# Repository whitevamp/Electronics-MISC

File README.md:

# Electronics-MISC
I do not own any of the files in this Git repository. I have placed them here for preservation and in the hope that they might be useful to someone. If any of these files belong to you and you would like them removed, please let me know. All these files were publicly available at the time of collection. Additionally, if you find any issues or have concerns about the content, please feel free to reach out to me for further assistance.

## License

This repository is licensed under the Creative Commons Attribution-NonCommercial-ShareAlike 4.0 International (CC BY-NC-SA 4.0). For more information, see the [LICENSE](LICENSE) file.

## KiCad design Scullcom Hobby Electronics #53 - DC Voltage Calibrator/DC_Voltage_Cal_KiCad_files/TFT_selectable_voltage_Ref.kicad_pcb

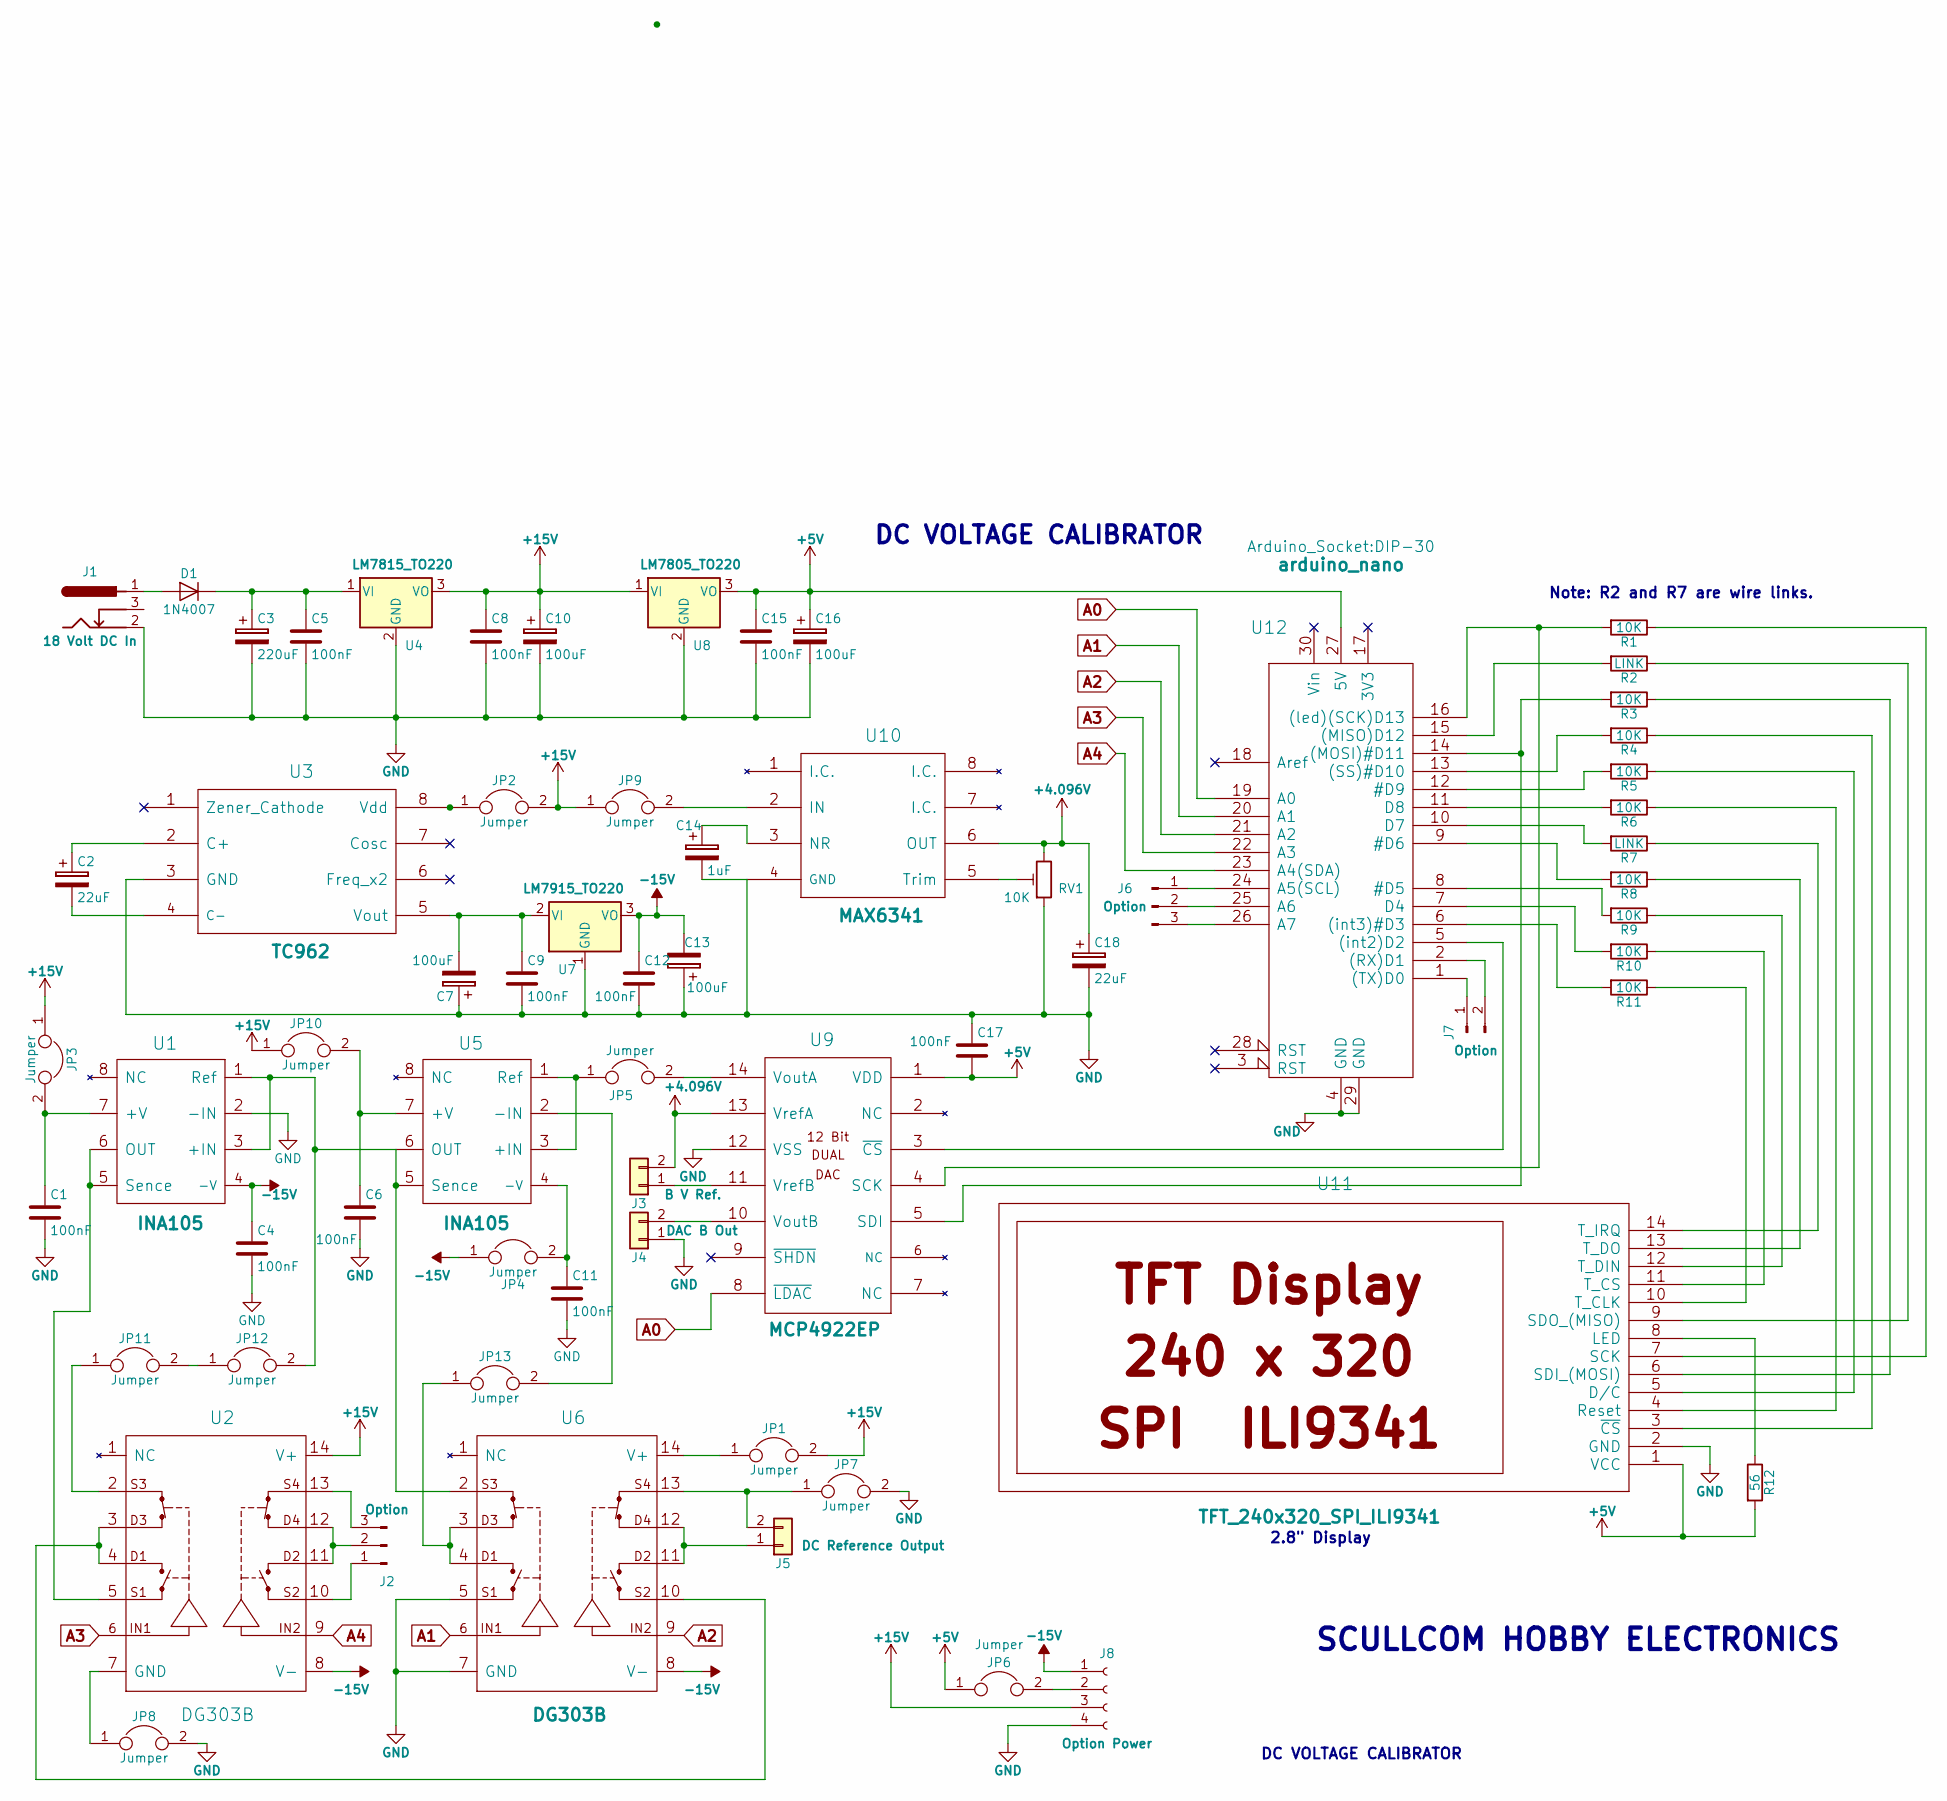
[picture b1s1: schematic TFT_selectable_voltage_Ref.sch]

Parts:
C1, C12: 100nF; C_Rect_L7.2mm_W2.5mm_P5.00mm_FKS2_FKP2_MKS2_MKP2
C2, C18: 22uF; CP_Radial_D5.0mm_P2.00mm
C3: 220uF; CP_Radial_D8.0mm_P5.00mm
C4, C5, C6, C8, C9, C11, C15, C17: 100nF; C_Rect_L7.0mm_W2.5mm_P5.00mm
C7, C10, C13, C16: 100uF; CP_Radial_D8.0mm_P2.50mm
C14: 1uF; CP_Radial_D5.0mm_P2.00mm
D1: 1N4007; D_T-1_P10.16mm_Horizontal
J1: 18 Volt DC In; BARREL_JACK
J2, J6: Option; Pin_Header_Straight_1x03_Pitch2.54mm
J3: B V Ref.; Pin_Header_Straight_1x02_Pitch2.54mm
J4: DAC B Out; Pin_Header_Straight_1x02_Pitch2.54mm
J5: DC Reference Output; Pin_Header_Straight_1x02_Pitch2.54mm
J7: Option; Pin_Header_Straight_1x02_Pitch2.54mm
J8: Option Power; Socket_Strip_Straight_1x04_Pitch2.54mm
JP1, JP2, JP3, JP4, JP5, JP6, JP7, JP8, JP9, JP10, JP11, JP12, JP13: Jumper; WireConnection_0.80mmDrill
R1, R3, R4, R5, R6, R8, R9, R10, R11: 10K; R_Axial_DIN0207_L6.3mm_D2.5mm_P10.16mm_Horizontal
R2, R7: LINK; R_Axial_DIN0207_L6.3mm_D2.5mm_P10.16mm_Horizontal
R12: 56; R_Axial_DIN0207_L6.3mm_D2.5mm_P10.16mm_Horizontal
RV1: 10K; Potentiometer_Trimmer_Bourns_3296X
U1, U5: INA105; DIP-8_W7.62mm_Socket_LongPads
U2, U6: DG303B; DIP-14_W7.62mm_Socket_LongPads
U3: TC962; DIP-8_W7.62mm_Socket_LongPads
U4: LM7815_TO220; TO-220
U7: LM7915_TO220; TO-220
U8: LM7805_TO220; TO-220
U9: MCP4922EP; DIP-14_W7.62mm_Socket_LongPads
U10: MAX6341; DIP-8_W7.62mm_Socket_LongPads
U11: TFT_240x320_SPI_ILI9341; Socket_Strip_Straight_1x14_Pitch2.54mm
U12: arduino_nano; DIP-30

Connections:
+4.096V: C18.1, J3.2, RV1.3, U9.13 (VrefA), U10.6 (OUT)
+5V: C15.1, C16.1, C17.2, JP6.1, R12.2, U8.3 (VO), U9.1 (VDD), U11.1 (VCC), U12.27 (5V)
+15V: C8.1, C10.1, J8.3, JP1.2, JP2.2, JP3.1, JP9.1, JP10.1, U2.14 (V+), U4.3 (VO), U8.1 (VI)
-15V: C4.1, C12.1, C13.2, J8.1, JP4.1, U1.4 (-V), U2.8 (V-), U6.8 (V-), U7.3 (VO)
A0: U9.8 (~LDAC), U12.19 (A0)
A1: U6.6, U12.20 (A1)
A2: U6.9, U12.21 (A2)
A3: U2.6, U12.22 (A3)
A4: U2.9, U12.23 (A4(SDA))
GND: C1.2, C3.2, C4.2, C5.2, C6.2, C7.1, C8.2, C9.2, C10.2, C11.2, C12.2, C13.1, C14.2, C15.2, C16.2, C17.1, C18.2, J1.2, J4.1, J8.4, JP7.2, JP8.2, RV1.1, U1.2 (-IN), U3.3 (GND), U4.2 (GND), U6.5, U6.7 (GND), U7.1 (GND), U8.2 (GND), U9.12 (VSS), U10.4 (GND), U11.2 (GND), U12.4 (GND), U12.29 (GND)
unnamed: C1.1, JP3.2, U1.7 (+V)
unnamed: C2.1, U3.2 (C+)
unnamed: C2.2, U3.4 (C-)
unnamed: C3.1, C5.1, D1.1 (K), U4.1 (VI)
unnamed: C6.1, JP10.2, U5.7 (+V)
unnamed: C7.2, C9.1, U3.5 (Vout), U7.2 (VI)
unnamed: C11.1, JP4.2, U5.4 (-V)
unnamed: C14.1, U10.3 (NR)
unnamed: D1.2 (A), J1.1
unnamed: J2.1, U2.10
unnamed: J2.2, U2.11, U2.12
unnamed: J2.3, U2.13
unnamed: J3.1, U9.11 (VrefB)
unnamed: J4.2, U9.10 (VoutB)
unnamed: J5.1, U6.11, U6.12
unnamed: J5.2, JP7.1, U6.13
unnamed: J6.1, U12.24 (A5(SCL))
unnamed: J6.2, U12.25 (A6)
unnamed: J6.3, U12.26 (A7)
unnamed: J7.1, U12.1 ((TX)D0)
unnamed: J7.2, U12.2 ((RX)D1)
unnamed: J8.2, JP6.2
unnamed: JP1.1, U6.14 (V+)
unnamed: JP2.1, U3.8 (Vdd)
unnamed: JP5.1, U5.1 (Ref), U5.3 (+IN)
unnamed: JP5.2, U9.14 (VoutA)
unnamed: JP8.1, U2.7 (GND)
unnamed: JP9.2, U10.2 (IN)
unnamed: JP11.1, U2.2
unnamed: JP11.2, JP12.1
unnamed: JP12.2, U1.1 (Ref), U1.3 (+IN), U5.5 (Sence), U5.6 (OUT), U6.2
unnamed: JP13.1, U6.3, U6.4
unnamed: JP13.2, U5.2 (-IN)
unnamed: R1.1, U11.7 (SCK)
unnamed: R1.2, U9.4 (SCK), U12.16 ((led)(SCK)D13)
unnamed: R2.1, U11.9 (SDO_(MISO))
unnamed: R2.2, U12.15 ((MISO)D12)
unnamed: R3.1, U11.6 (SDI_(MOSI))
unnamed: R3.2, U9.5 (SDI), U12.14 ((MOSI)#D11)
unnamed: R4.1, U11.3 (~CS)
unnamed: R4.2, U12.13 ((SS)#D10)
unnamed: R5.1, U11.5 (D/C)
unnamed: R5.2, U12.12 (#D9)
unnamed: R6.1, U11.4 (Reset)
unnamed: R6.2, U12.11 (D8)
unnamed: R7.1, U11.14 (T_IRQ)
unnamed: R7.2, U12.10 (D7)
unnamed: R8.1, U11.13 (T_DO)
unnamed: R8.2, U12.9 (#D6)
unnamed: R9.1, U11.12 (T_DIN)
unnamed: R9.2, U12.8 (#D5)
unnamed: R10.1, U11.11 (T_CS)
unnamed: R10.2, U12.7 (D4)
unnamed: R11.1, U11.10 (T_CLK)
unnamed: R11.2, U12.6 ((int3)#D3)
unnamed: R12.1, U11.8 (LED)
unnamed: RV1.2, U10.5 (Trim)
unnamed: U1.5 (Sence), U1.6 (OUT), U2.5
unnamed: U2.3, U2.4, U6.10
unnamed: U9.3 (~CS), U12.5 ((int2)D2)

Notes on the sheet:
Note: R2 and R7 are wire links.
2.8" Display
DC VOLTAGE CALIBRATOR
SCULLCOM HOBBY ELECTRONICS

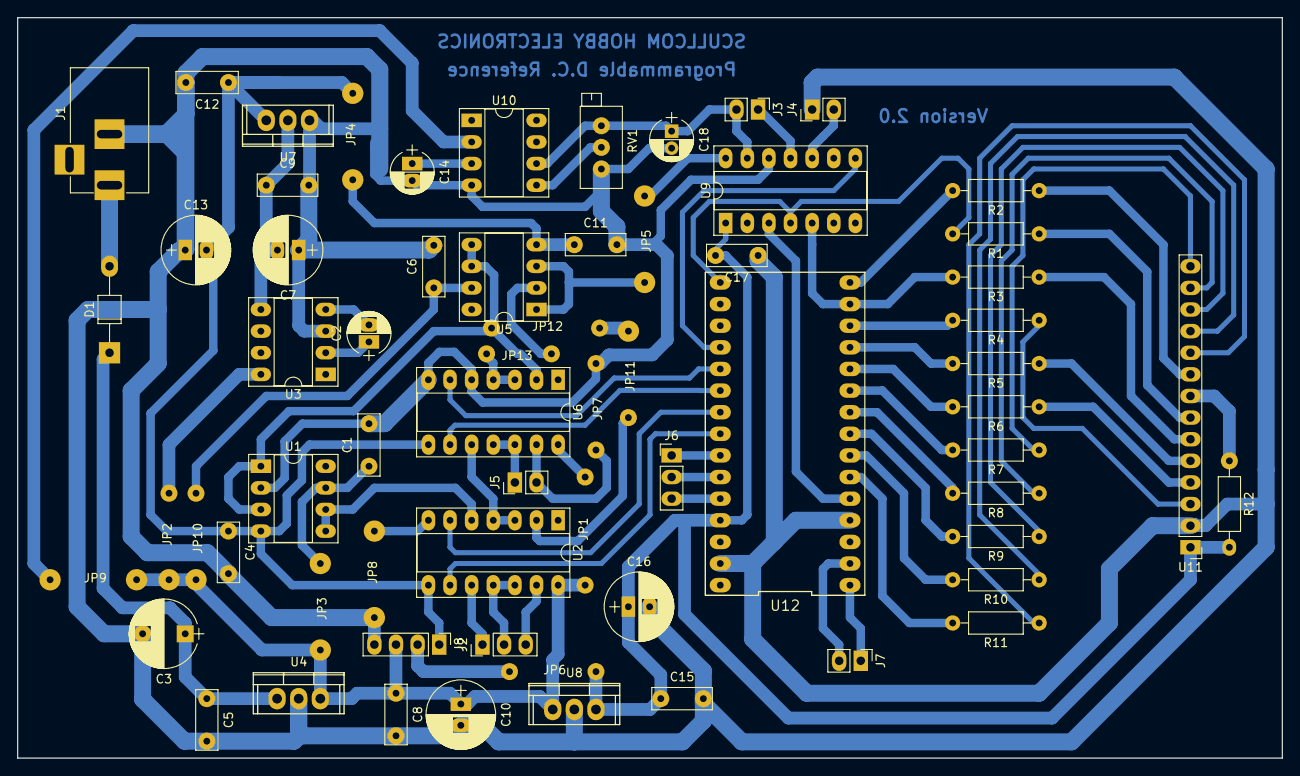
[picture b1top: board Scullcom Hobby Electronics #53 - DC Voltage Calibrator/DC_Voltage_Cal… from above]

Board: 2 copper layers, 148.6 x 87.0 mm, 65 parts (0 on the bottom side), 70 nets.

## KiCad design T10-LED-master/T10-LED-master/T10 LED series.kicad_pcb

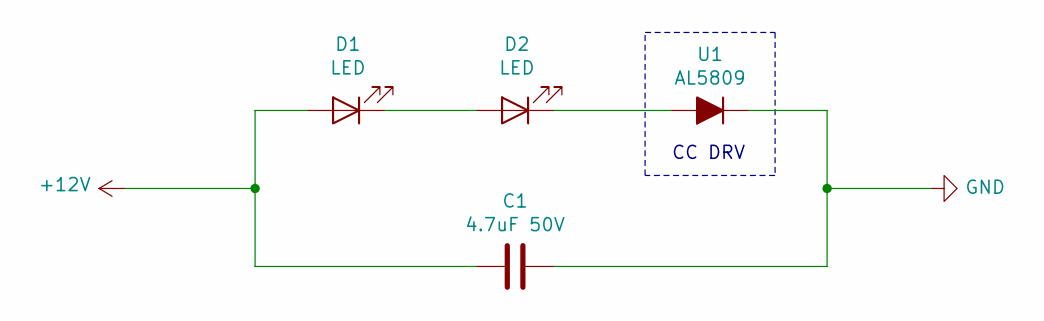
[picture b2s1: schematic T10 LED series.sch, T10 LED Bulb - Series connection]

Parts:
C1: 4.7uF 50V; C_1206_3216Metric; Part Number GCJ31CC71H475KA01L
D1, D2: LED; LED_PLCC_2835
U1: AL5809; D_PowerDI-123

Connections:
+12V: C1.1, D1.2 (A)
GND: C1.2, U1.1 (K)
unnamed: D1.1 (K), D2.2 (A)
unnamed: D2.1 (K), U1.2 (A)

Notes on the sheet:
CC DRV

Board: 2 copper layers, 4 parts (2 on the bottom side), 4 nets, no tracks yet.

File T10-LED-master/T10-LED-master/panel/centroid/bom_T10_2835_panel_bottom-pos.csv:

Ref,Val,Package,PosX,PosY,Rot,Side
"D2","LED","LED_PLCC_2835",109.150000,-54.400000,270.000000,bottom
"D2","LED","LED_PLCC_2835",96.250000,-81.400000,270.000000,bottom
"D2","LED","LED_PLCC_2835",134.950000,-81.400000,270.000000,bottom
"D2","LED","LED_PLCC_2835",147.850000,-81.400000,270.000000,bottom
"D2","LED","LED_PLCC_2835",160.750000,-81.400000,270.000000,bottom
"D2","LED","LED_PLCC_2835",173.650000,-81.400000,270.000000,bottom
"D2","LED","LED_PLCC_2835",109.150000,-81.400000,270.000000,bottom
"D2","LED","LED_PLCC_2835",122.050000,-81.400000,270.000000,bottom
"D2","LED","LED_PLCC_2835",173.650000,-54.400000,270.000000,bottom
"D2","LED","LED_PLCC_2835",160.750000,-54.400000,270.000000,bottom
"D2","LED","LED_PLCC_2835",147.850000,-54.400000,270.000000,bottom
"D2","LED","LED_PLCC_2835",134.950000,-54.400000,270.000000,bottom
"D2","LED","LED_PLCC_2835",122.050000,-54.400000,270.000000,bottom
"D2","LED","LED_PLCC_2835",96.250000,-108.400000,270.000000,bottom
"D2","LED","LED_PLCC_2835",160.750000,-108.400000,270.000000,bottom
"D2","LED","LED_PLCC_2835",147.850000,-108.400000,270.000000,bottom
"D2","LED","LED_PLCC_2835",173.650000,-108.400000,270.000000,bottom
"D2","LED","LED_PLCC_2835",109.150000,-108.400000,270.000000,bottom
"D2","LED","LED_PLCC_2835",122.050000,-108.400000,270.000000,bottom
"D2","LED","LED_PLCC_2835",134.950000,-108.400000,270.000000,bottom
"D2","LED","LED_PLCC_2835",96.250000,-54.400000,270.000000,bottom
"REF**","Fiducial_0.75mm_Mask1.5mm","Fiducial_0.75mm_Mask1.5mm",171.000000,-133.900000,180.000000,bottom
"REF**","Fiducial_0.75mm_Mask1.5mm","Fiducial_0.75mm_Mask1.5mm",86.500000,-65.400000,90.000000,bottom
"REF**","Fiducial_0.75mm_Mask1.5mm","Fiducial_0.75mm_Mask1.5mm",167.000000,-42.900000,0.000000,bottom
"U1","AL5809","D_PowerDI-123",147.850000,-63.400000,180.000000,bottom
"U1","AL5809","D_PowerDI-123",134.950000,-63.400000,180.000000,bottom
"U1","AL5809","D_PowerDI-123",96.250000,-63.400000,180.000000,bottom
"U1","AL5809","D_PowerDI-123",122.050000,-63.400000,180.000000,bottom
"U1","AL5809","D_PowerDI-123",109.150000,-63.400000,180.000000,bottom
"U1","AL5809","D_PowerDI-123",147.850000,-117.400000,180.000000,bottom
"U1","AL5809","D_PowerDI-123",160.750000,-63.400000,180.000000,bottom
"U1","AL5809","D_PowerDI-123",173.650000,-63.400000,180.000000,bottom
"U1","AL5809","D_PowerDI-123",96.250000,-90.400000,180.000000,bottom
"U1","AL5809","D_PowerDI-123",122.050000,-90.400000,180.000000,bottom
"U1","AL5809","D_PowerDI-123",160.750000,-90.400000,180.000000,bottom
"U1","AL5809","D_PowerDI-123",173.650000,-90.400000,180.000000,bottom
"U1","AL5809","D_PowerDI-123",134.950000,-90.400000,180.000000,bottom
"U1","AL5809","D_PowerDI-123",147.850000,-90.400000,180.000000,bottom
"U1","AL5809","D_PowerDI-123",109.150000,-90.400000,180.000000,bottom
"U1","AL5809","D_PowerDI-123",96.250000,-117.400000,180.000000,bottom
"U1","AL5809","D_PowerDI-123",122.050000,-117.400000,180.000000,bottom
"U1","AL5809","D_PowerDI-123",160.750000,-117.400000,180.000000,bottom
"U1","AL5809","D_PowerDI-123",173.650000,-117.400000,180.000000,bottom
"U1","AL5809","D_PowerDI-123",134.950000,-117.400000,180.000000,bottom
"U1","AL5809","D_PowerDI-123",109.150000,-117.400000,180.000000,bottom

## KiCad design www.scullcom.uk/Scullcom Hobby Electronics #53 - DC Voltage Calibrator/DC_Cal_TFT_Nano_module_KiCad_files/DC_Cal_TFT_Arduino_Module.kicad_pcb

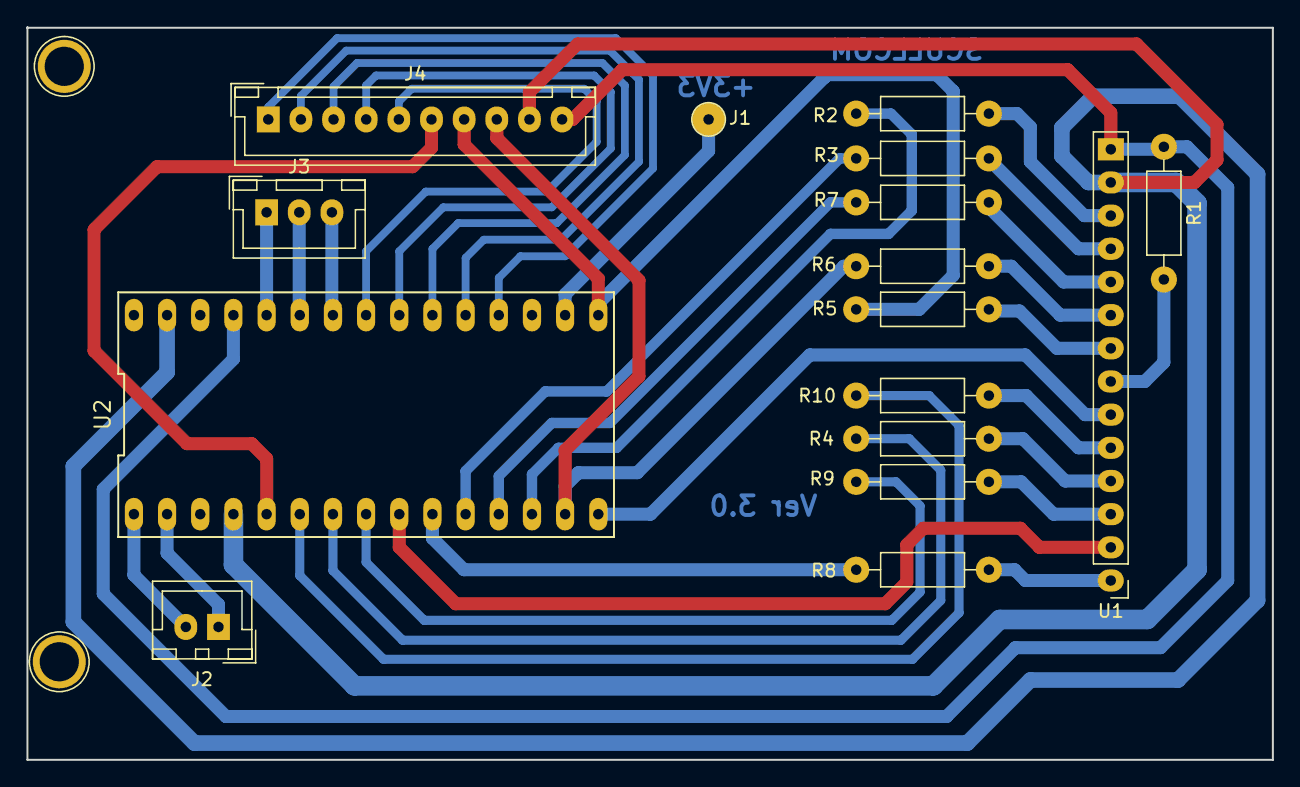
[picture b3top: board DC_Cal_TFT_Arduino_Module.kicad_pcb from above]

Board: 2 copper layers, 95.4 x 56.1 mm, 16 parts (0 on the bottom side), 35 nets.

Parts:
J1: +3V3 output (option); 1pin
J2: Upgrade Option; JST_XH_B02B-XH-A_02x2.50mm_Straight
J3: Upgrade Option; JST_XH_B03B-XH-A_03x2.50mm_Straight
J4: Input from Main PCB; JST_XH_B10B-XH-A_10x2.50mm_Straight
R1: 56; R_Axial_DIN0207_L6.3mm_D2.5mm_P10.16mm_Horizontal
R2, R3, R4, R5, R6, R7, R8, R9, R10: 10K; R_Axial_DIN0207_L6.3mm_D2.5mm_P10.16mm_Horizontal
U1: TFT_240x320_SPI_ILI9341; Pin_Header_Straight_1x14_Pitch2.54mm
U2: arduino_nano; DIP-30_0_ELL

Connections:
+5V: J4.10, R1.1, U1.1, U2.27
GND: J4.9, U1.2, U2.4, U2.29
unnamed: J1.1, U2.17
unnamed: J2.1, U2.2
unnamed: J2.2, U2.1
unnamed: J3.1, U2.26
unnamed: J3.2, U2.25
unnamed: J3.3, U2.24
unnamed: J4.1, U2.19
unnamed: J4.2, U2.20
unnamed: J4.3, U2.21
unnamed: J4.4, U2.22
unnamed: J4.5, U2.23
unnamed: J4.6, U2.5
unnamed: J4.7, R5.1, U2.16
unnamed: J4.8, R6.1, U2.14
unnamed: R1.2, U1.8
unnamed: R2.1, U2.13
unnamed: R2.2, U1.3
unnamed: R3.1, U2.11
unnamed: R3.2, U1.4
unnamed: R4.1, U2.7
unnamed: R4.2, U1.11
unnamed: R5.2, U1.7
unnamed: R6.2, U1.6
unnamed: R7.1, U2.12
unnamed: R7.2, U1.5
unnamed: R8.1, U2.10
unnamed: R8.2, U1.14
unnamed: R9.1, U2.8
unnamed: R9.2, U1.12
unnamed: R10.1, U2.6
unnamed: R10.2, U1.10
unnamed: U1.9, U2.15
unnamed: U1.13, U2.9

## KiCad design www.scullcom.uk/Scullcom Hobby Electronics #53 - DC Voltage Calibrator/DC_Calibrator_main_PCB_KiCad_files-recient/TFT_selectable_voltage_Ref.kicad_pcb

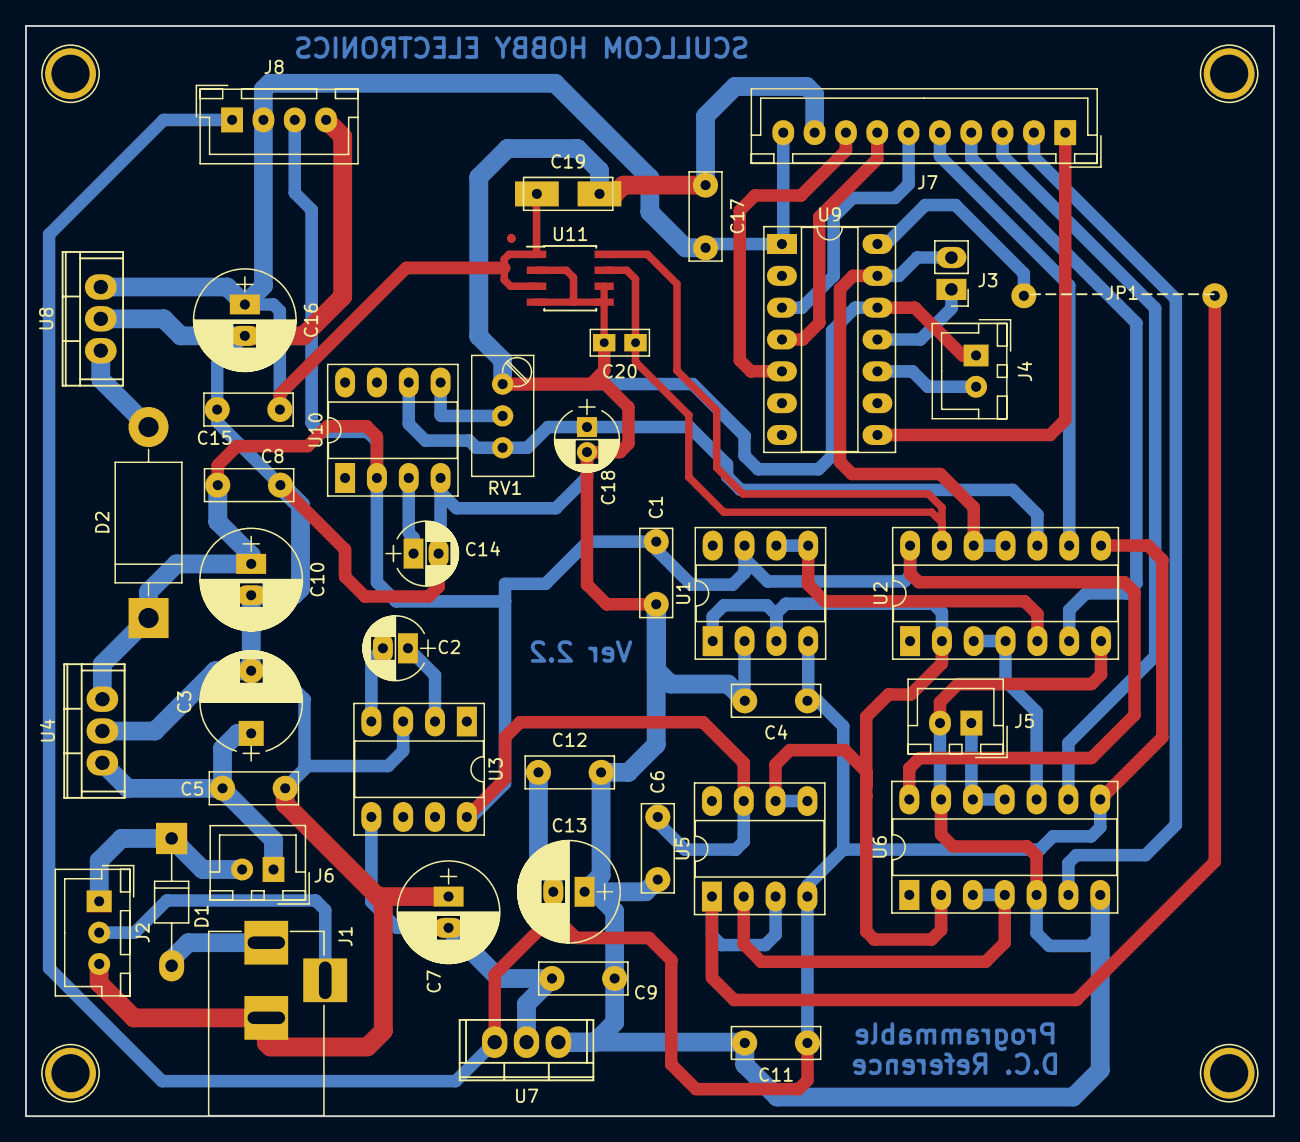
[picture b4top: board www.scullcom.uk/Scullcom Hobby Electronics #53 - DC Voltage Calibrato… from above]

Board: 2 copper layers, 99.6 x 87.0 mm, 43 parts (0 on the bottom side), 34 nets.

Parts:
-----JP1-----: Jumper; WireConnection_0.80mmDrill
C1, C4, C5, C6, C8, C9, C11, C12, C15, C17: 100nF; C_Rect_L7.0mm_W2.5mm_P5.00mm
C2, C18: 22uF; CP_Radial_D5.0mm_P2.00mm
C3: 220uF; CP_Radial_D8.0mm_P5.00mm
C7, C10, C13, C16: 100uF; CP_Radial_D8.0mm_P2.50mm
C14: 1uF; CP_Radial_D5.0mm_P2.00mm
C19: 2.2uF; C_Rect_L7.0mm_W2.5mm_P5.00mm
C20: 220pF; C_Rect_L4.6mm_W2.0mm_P2.50mm_MKS02_FKP02
D1: 1N4007; D_T-1_P10.16mm_Horizontal
D2: 1N5338B; D_DO-201AD_P15.24mm_Horizontal
J1: 18 Volt DC In; BARREL_JACK
J2: Battery; JST_XH_B03B-XH-A_03x2.50mm_Straight
J3: B Vref.; Pin_Header_Straight_1x02_Pitch2.54mm
J4: DAC B Out; JST_XH_B02B-XH-A_02x2.50mm_Straight
J5: DC Reference Output; JST_XH_B02B-XH-A_02x2.50mm_Straight
J6: On/Off Switch; JST_XH_B02B-XH-A_02x2.50mm_Straight
J7: To Display/Nano; JST_XH_B10B-XH-A_10x2.50mm_Straight
J8: Option Power; JST_XH_B04B-XH-A_04x2.50mm_Straight
RV1: 10K; Potentiometer_Trimmer_Bourns_3296W
U1, U5: INA105; DIP-8_W7.62mm_Socket_LongPads
U2, U6: DG303B; DIP-14_W7.62mm_Socket_LongPads
U3: TC962; DIP-8_W7.62mm_Socket_LongPads
U4: LM7815_TO220; TO-220
U7: LM7915_TO220; TO-220
U8: LM7805_TO220; TO-220
U9: MCP4922EP; DIP-14_W7.62mm_Socket_LongPads
U10: MAX6341; DIP-8_W7.62mm_Socket_LongPads
U11: MCP1501_10; SOIC-8_3.9x4.9mm_Pitch1.27mm

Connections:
+1.024V: C20.1, U2.13, U11.7, U11.8
+4.096V: C18.1, RV1.3, U2.10, U10.6
+5V: C15.1, C16.1, C17.2, C19.1, J7.10, J8.2, U8.3, U9.1, U11.1, U11.3
+15V: C1.1, C6.1, C8.1, C10.1, D2.1, J8.3, U1.7, U2.14, U3.8, U4.3, U5.7, U6.14, U10.2
-15V: C4.1, C11.1, C12.1, C13.2, J8.1, U1.4, U2.8, U5.4, U6.8, U7.3
A0: J7.1, U9.8
A1: J7.2, U6.6
A2: J7.3, U6.9
A3: J7.4, U2.6
A4: J7.5, U2.9
GND: C1.2, C3.2, C4.2, C5.2, C6.2, C7.1, C8.2, C9.2, C10.2, C11.2, C12.2, C13.1, C14.2, C15.2, C16.2, C17.1, C18.2, C19.2, C20.2, J1.2, J2.3, J4.1, J5.2, J7.9, J8.4, RV1.1, U1.2, U2.7, U3.3, U4.2, U6.5, U6.7, U6.13, U7.1, U8.2, U9.12, U10.4, U11.2, U11.4, U11.5, U11.6
unnamed: C2.1, U3.2
unnamed: C2.2, U3.4
unnamed: C3.1, C5.1, J6.1, U4.1
unnamed: C7.2, C9.1, U3.5, U7.2
unnamed: C14.1, U10.3
unnamed: D1.1, J2.1, J6.2
unnamed: D1.2, J1.1
unnamed: D2.2, U8.1
unnamed: J1.3, J2.2
unnamed: J3.1, U9.11
unnamed: J4.2, U9.10
unnamed: J5.1, U6.11, U6.12
unnamed: J7.6, U9.3
unnamed: J7.7, U9.4
unnamed: J7.8, U9.5
unnamed: -----JP1-----.1, U5.1, U5.3
unnamed: -----JP1-----.2, U9.14
unnamed: RV1.2, U10.5
unnamed: U1.1, U1.3, U2.2, U5.5, U5.6, U6.2
unnamed: U1.5, U1.6, U2.5
unnamed: U2.3, U2.4, U6.10
unnamed: U5.2, U6.3, U6.4
Vref: J3.2, U2.11, U2.12, U9.13

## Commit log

2024-06-20 first commit.
2024-06-20 second commit.
2024-06-20 added some files and reorganized some files and folders.
2024-06-20 third commit.
2024-06-20 4th adding files.
2024-06-20 files added
2024-06-20 added keycad footprints 1
2024-06-20 more files added
2024-06-20 more kicad files added
2024-06-20 more kicad files
2024-06-20 removed kicad file's. the kicad files can be found at the kicad gitlab site. https://gitlab.com/kicad/libraries
